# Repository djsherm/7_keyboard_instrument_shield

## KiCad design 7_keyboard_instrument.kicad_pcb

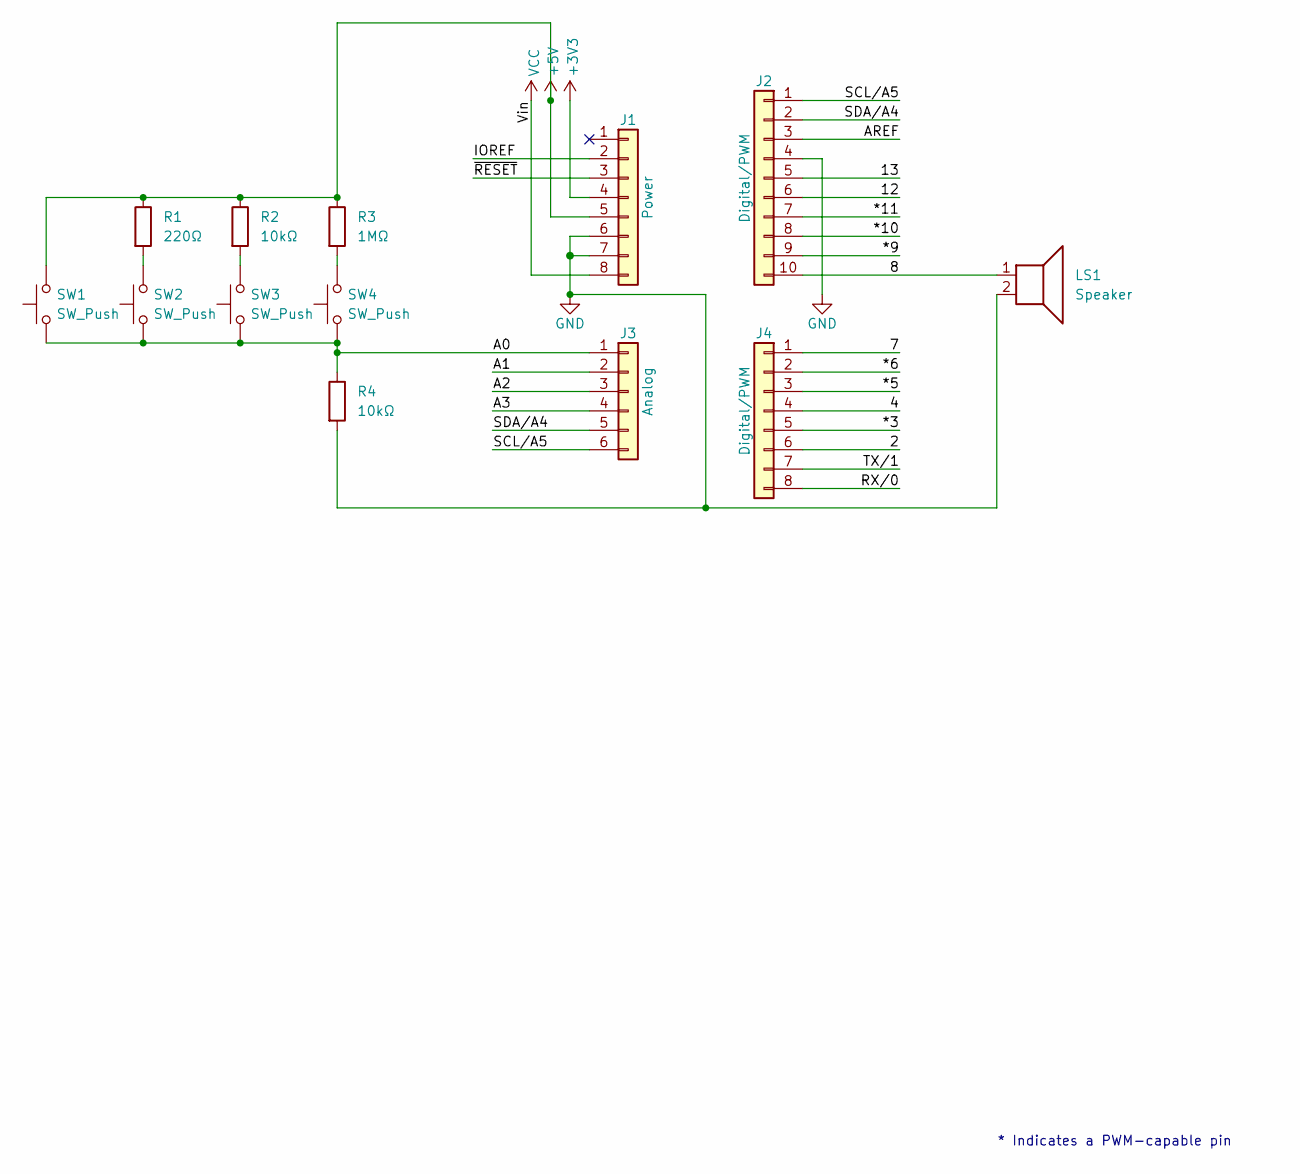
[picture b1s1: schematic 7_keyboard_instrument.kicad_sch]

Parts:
J1: Power; PinSocket_1x08_P2.54mm_Vertical
J2: Digital/PWM; PinSocket_1x10_P2.54mm_Vertical
J3: Analog; PinSocket_1x06_P2.54mm_Vertical
J4: Digital/PWM; PinSocket_1x08_P2.54mm_Vertical
LS1: Speaker; speaker
R1: 220Ω; R_Axial_DIN0207_L6.3mm_D2.5mm_P10.16mm_Horizontal
R2, R4: 10kΩ; R_Axial_DIN0207_L6.3mm_D2.5mm_P10.16mm_Horizontal
R3: 1MΩ; R_Axial_DIN0207_L6.3mm_D2.5mm_P10.16mm_Horizontal
SW1, SW2, SW3, SW4: SW_Push; TS02 push button

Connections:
+3V3: J1.4
+5V: J1.5, R1.1, R2.1, R3.1, SW1.2
/2: J4.6
/4: J4.4
/7: J4.1
/8: J2.10, LS1.1
/12: J2.6
/13: J2.5
/*3: J4.5
/*5: J4.3
/*6: J4.2
/*9: J2.9
/*10: J2.8
/*11: J2.7
/A0: J3.1, R4.1, SW1.1, SW2.1, SW3.1, SW4.1
/A1: J3.2
/A2: J3.3
/A3: J3.4
/AREF: J2.3
/IOREF: J1.2
/RX/0: J4.8
/SCL/A5: J2.1, J3.6
/SDA/A4: J2.2, J3.5
/TX/1: J4.7
/~RESET: J1.3
GND: J1.6, J1.7, J2.4, LS1.2, R4.2
unnamed: R1.2, SW2.2
unnamed: R2.2, SW3.2
unnamed: R3.2, SW4.2
VCC: J1.8

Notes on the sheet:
* Indicates a PWM-capable pin

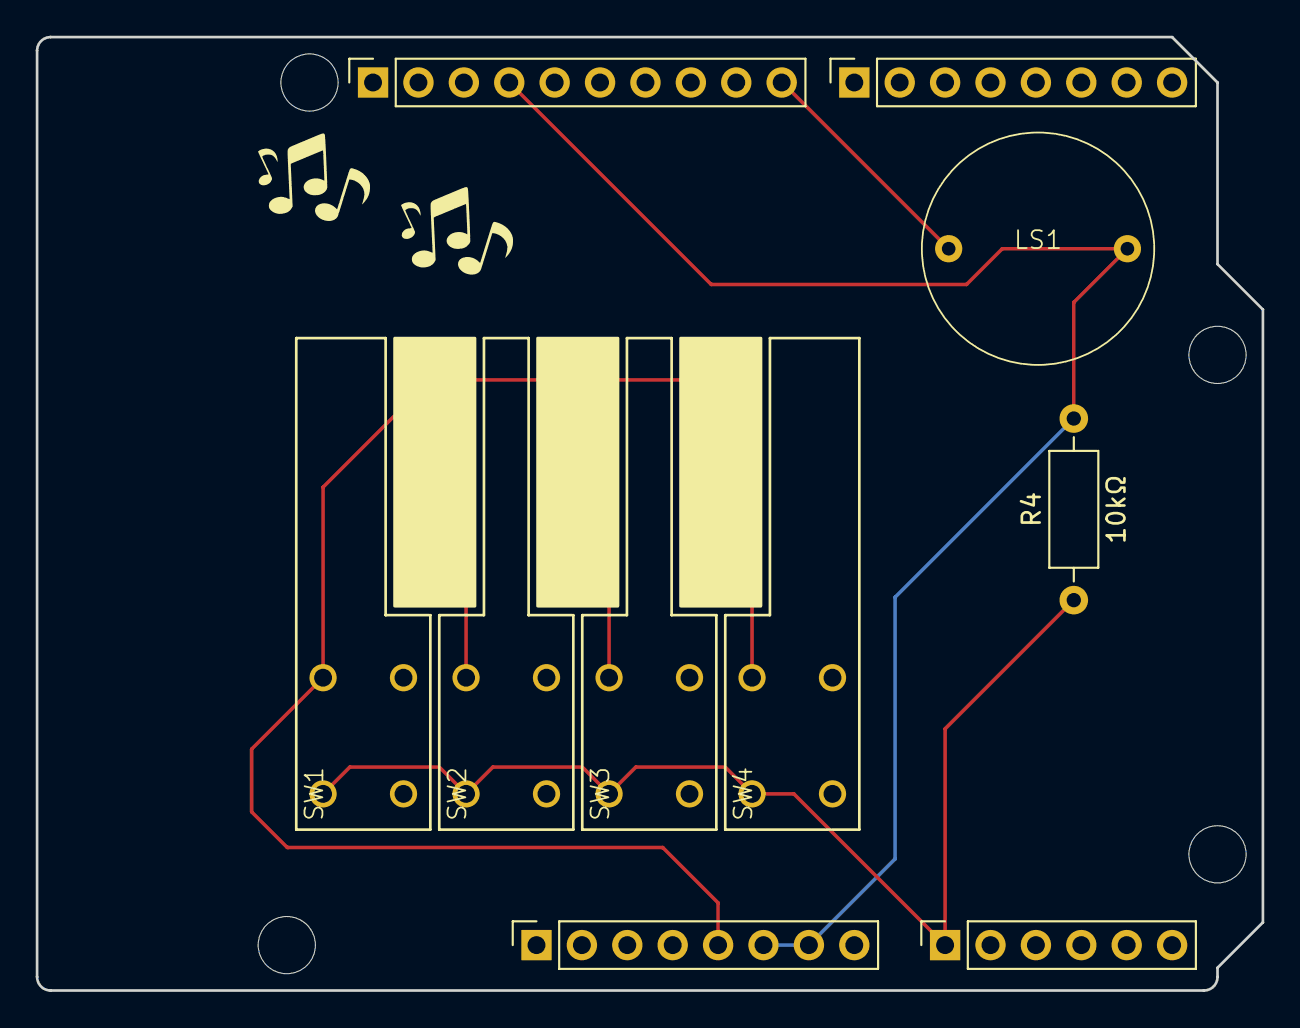
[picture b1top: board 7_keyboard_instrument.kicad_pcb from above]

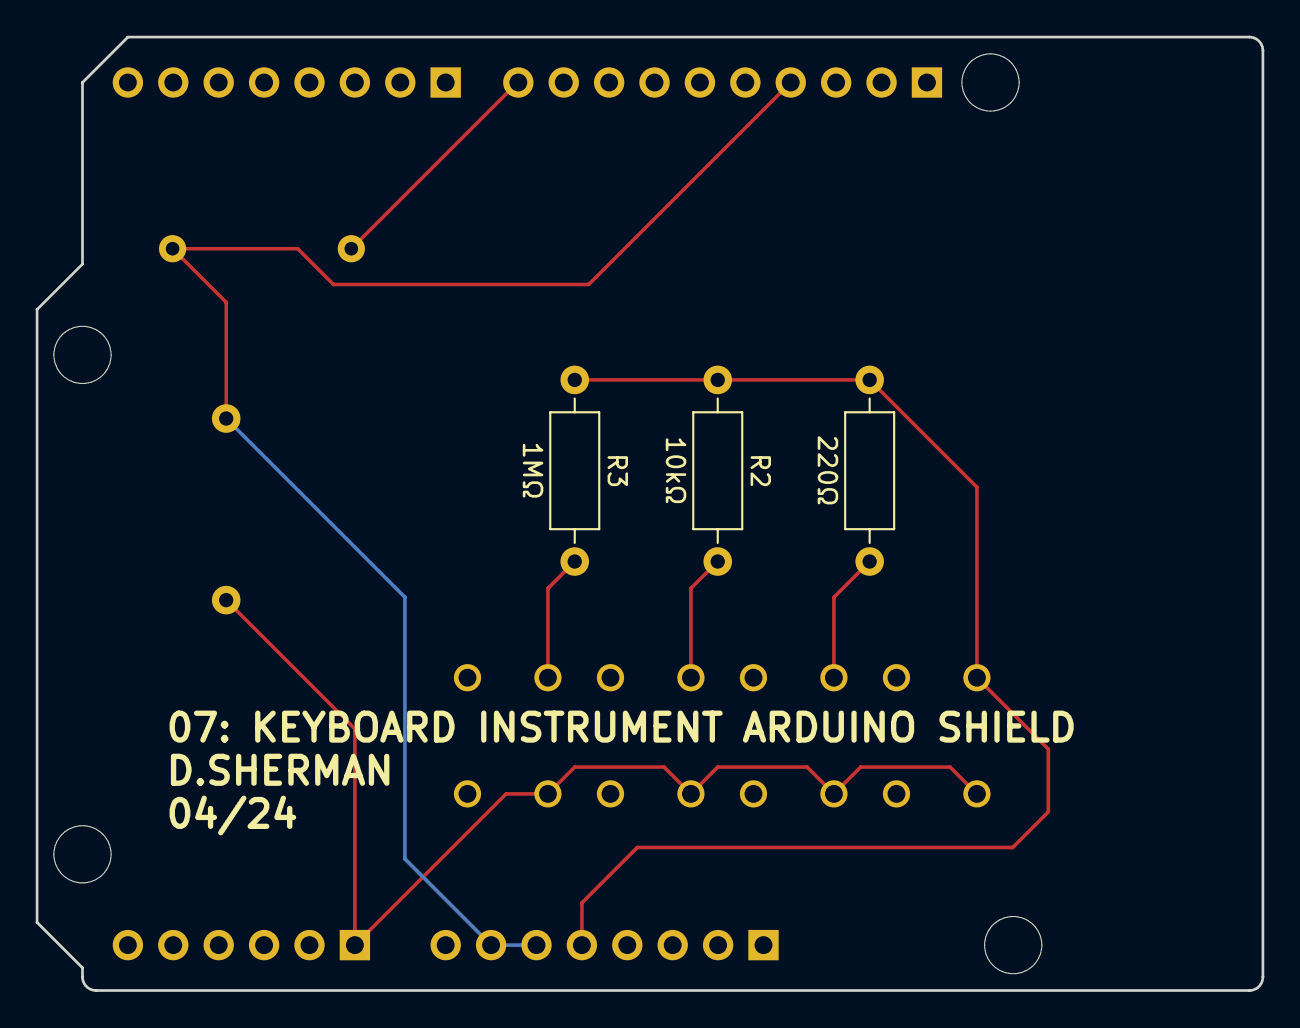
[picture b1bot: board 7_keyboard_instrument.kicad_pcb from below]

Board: 2 copper layers, 68.6 x 53.3 mm, 17 parts (3 on the bottom side), 9 nets.

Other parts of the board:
MH1, MH2, MH3, MH4: MountingHole_3.2mm
